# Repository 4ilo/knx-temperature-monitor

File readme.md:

# KNX temperature monitor

Custom Pt100 temperature probe interface to KNX.

This module will be used to monitor my pool temperature, and generate alarms if the pump, water treatement or the pool heating stops.

### Features
- STM32F0 microcontroller
- On module LCD temperature readout (Nokia 5110 Lcd)
- Tapko KIMaip KNX bus interface module
- MAX31865 RTD-to-Digital Converter
- Extra binary I/O

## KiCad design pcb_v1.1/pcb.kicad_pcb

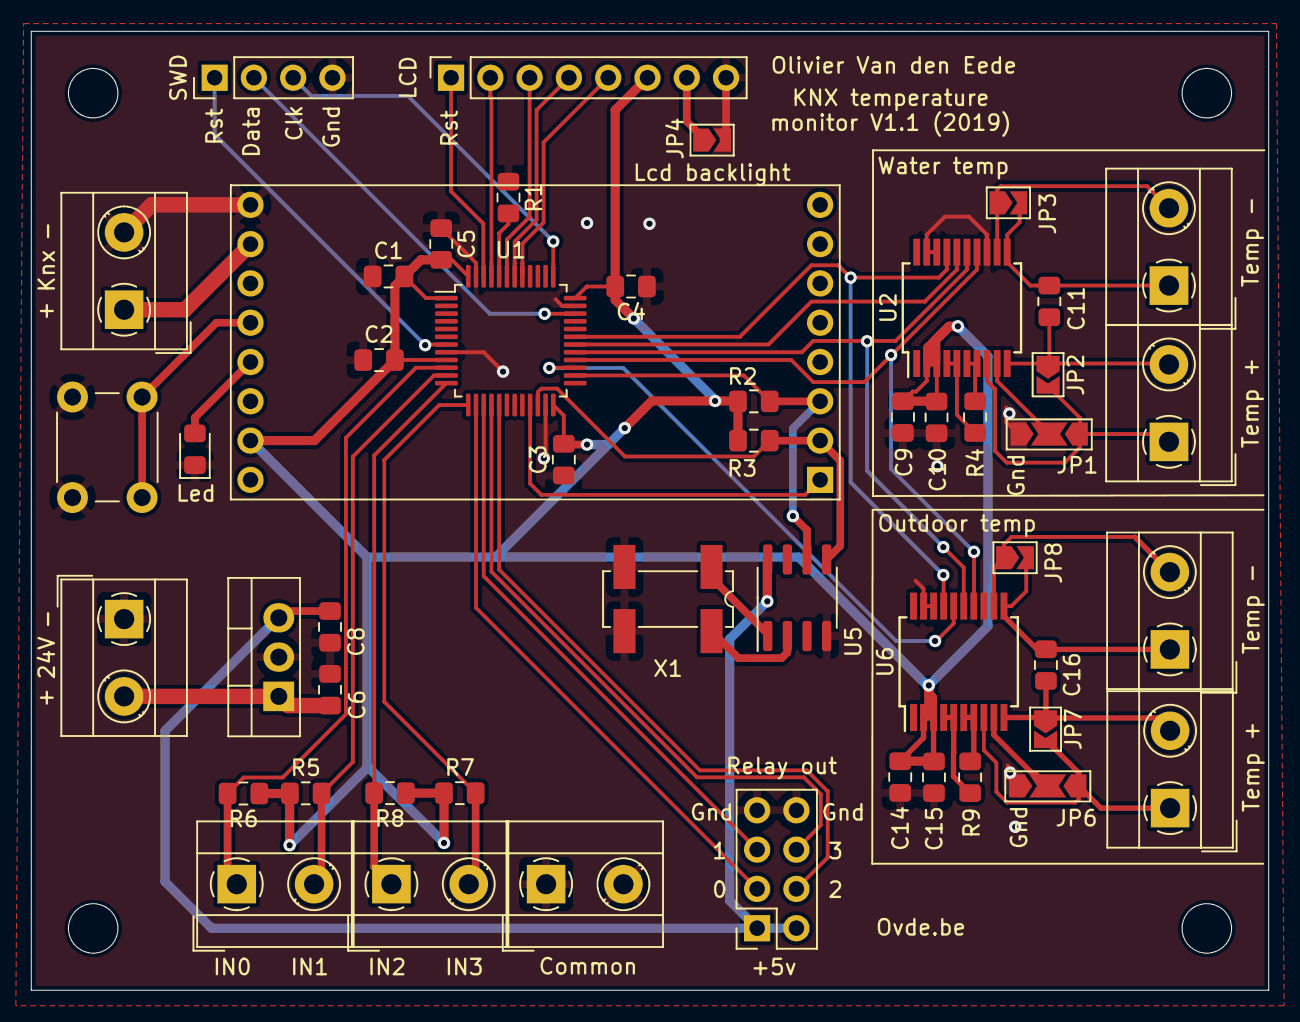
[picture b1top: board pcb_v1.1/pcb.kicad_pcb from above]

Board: 2 copper layers, 80.0 x 62.0 mm, 50 parts (0 on the bottom side), 49 nets.

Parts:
24V: 24v; TerminalBlock_MetzConnect_Type055_RT01502HDWU_1x02_P5.00mm_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
A1: KIMaip
C1, C2, C3, C4, C5, C8, C9, C10, C11, C14, C15, C16: 0.1uf; C_0805_2012Metric_Pad1.15x1.40mm_HandSolder
C6: 0.33uf; C_0805_2012Metric_Pad1.15x1.40mm_HandSolder
Common: Screw_Terminal_01x02; TerminalBlock_MetzConnect_Type055_RT01502HDWU_1x02_P5.00mm_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
J4, J5: Screw_Terminal_01x02; TerminalBlock_MetzConnect_Type055_RT01502HDWU_1x02_P5.00mm_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
JP1, JP6: SolderJumper_3_Open; SolderJumper-3_P2.0mm_Open_TrianglePad1.0x1.5mm_NumberLabels
JP2, JP3, JP4, JP7, JP8: SolderJumper_2_Open; SolderJumper-2_P1.3mm_Open_TrianglePad1.0x1.5mm
Knx: Knx; TerminalBlock_MetzConnect_Type055_RT01502HDWU_1x02_P5.00mm_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
LCD: Nokia 5110 LCD; PinSocket_1x08_P2.54mm_Vertical
Led: LED_ALT; LED_0805_2012Metric_Pad1.15x1.40mm_HandSolder
R1: 10k; R_0805_2012Metric_Pad1.15x1.40mm_HandSolder
R2, R3, R5, R6, R7, R8: 4k7; R_0805_2012Metric_Pad1.15x1.40mm_HandSolder
R4, R9: 420; R_0805_2012Metric_Pad1.15x1.40mm_HandSolder
Relay out: Relay out; PinSocket_2x04_P2.54mm_Vertical
SW1: SW_Push_Dual; SW_PUSH_6mm
SWD: SWD; PinHeader_1x04_P2.54mm_Vertical
Temp +: Screw_Terminal_01x02; TerminalBlock_MetzConnect_Type055_RT01502HDWU_1x02_P5.00mm_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
Temp +#2: Screw_Terminal_01x02; TerminalBlock_MetzConnect_Type055_RT01502HDWU_1x02_P5.00mm_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
Temp -: Screw_Terminal_01x02; TerminalBlock_MetzConnect_Type055_RT01502HDWU_1x02_P5.00mm_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
Temp -#2: Screw_Terminal_01x02; TerminalBlock_MetzConnect_Type055_RT01502HDWU_1x02_P5.00mm_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
U1: STM32F072C8Tx; LQFP-48_7x7mm_P0.5mm
U2, U6: MAX31865; SSOP-20_5.3x7.2mm_P0.65mm
U3: LM7805_TO220; TO-220-3_Vertical
U5: DS1307Z+; SOIC-8_3.9x4.9mm_P1.27mm
X1: 32.768kHz; Crystal_SMD_SeikoEpson_MC306-4Pin_8.0x3.2mm_HandSoldering

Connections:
+3V3: A1.15, C1.2, C2.2, C3.2, C4.2, C5.2, C9.2, C10.2, C14.2, C15.2, LCD.6, R2.1, R3.1, R5.1, R6.1, R7.1, R8.1, U1.1, U1.9, U1.24, U1.36, U1.48, U2.2, U2.3, U6.2, U6.3
+5V: C8.2, Relay out.1, Relay out.2, U3.3, U5.8
+24V: 24V.2, C6.2, U3.1
/BIN_0: J4.1, R6.2, U1.10
/BIN_1: J4.2, R5.2, U1.11
/BIN_2: J5.1, R8.2, U1.12
/BIN_3: J5.2, R7.2, U1.13
/CLK_1: U1.29, U2.15, U6.15
/DRDY: A1.1, U1.21
/Key: A1.12, SW1.1
/LCD_CE: LCD.2, U1.45
/LCD_CLK: LCD.5, U1.41
/LCD_DATA: LCD.4, U1.42
/LCD_DC: LCD.3, U1.43
/LCD_RST: LCD.1, U1.46
/MISO_1: U1.31, U2.17, U6.17
/MOSI_1: U1.28, U2.14, U6.14
/NRST: SWD.1, U1.7
/OUT_0: Relay out.3, U1.14
/OUT_1: Relay out.5, U1.15
/OUT_2: Relay out.4, U1.17
/OUT_3: Relay out.6, U1.16
/SCL: A1.3, R2.2, U1.26, U5.6
/SDA: A1.2, R3.2, U1.22, U5.5
/SS_1: U1.30, U2.16
/SS_2: U1.27, U6.16
/SWDCLK: SWD.3, U1.37
/SWDIO: SWD.2, U1.34
GND: 24V.1, A1.9, C1.1, C2.1, C3.1, C4.1, C5.1, C6.1, C8.1, C9.1, C10.1, C14.1, C15.1, Common.1, Common.2, JP1.3, JP4.2, JP6.3, Knx.2, LCD.8, Led.1, R1.1, Relay out.7, Relay out.8, SW1.2, SWD.4, U1.8, U1.23, U1.35, U1.47, U2.13, U2.18, U2.19, U3.2, U5.4, U6.13, U6.18, U6.19, X1.2, X1.3
unnamed: A1.10, Knx.1
unnamed: A1.13, Led.2
unnamed: C11.1, JP2.1, Temp +.2, U2.10
unnamed: C11.2, JP3.2, Temp -.1, U2.11
unnamed: C16.1, JP7.1, Temp +#2.2, U6.10
unnamed: C16.2, JP8.2, Temp -#2.1, U6.11
unnamed: JP4.1, LCD.7
unnamed: JP1.1, JP2.2, Temp +.1, U2.8
unnamed: JP3.1, Temp -.2, U2.12
unnamed: JP6.1, JP7.2, Temp +#2.1, U6.8
unnamed: JP8.1, Temp -#2.2, U6.12
unnamed: JP1.2, U2.9
unnamed: JP6.2, U6.9
unnamed: R1.2, U1.44
unnamed: R4.1, U2.4, U2.5
unnamed: R4.2, U2.6, U2.7
unnamed: R9.1, U6.4, U6.5
unnamed: R9.2, U6.6, U6.7
unnamed: U5.1, X1.1
unnamed: U5.2, X1.4

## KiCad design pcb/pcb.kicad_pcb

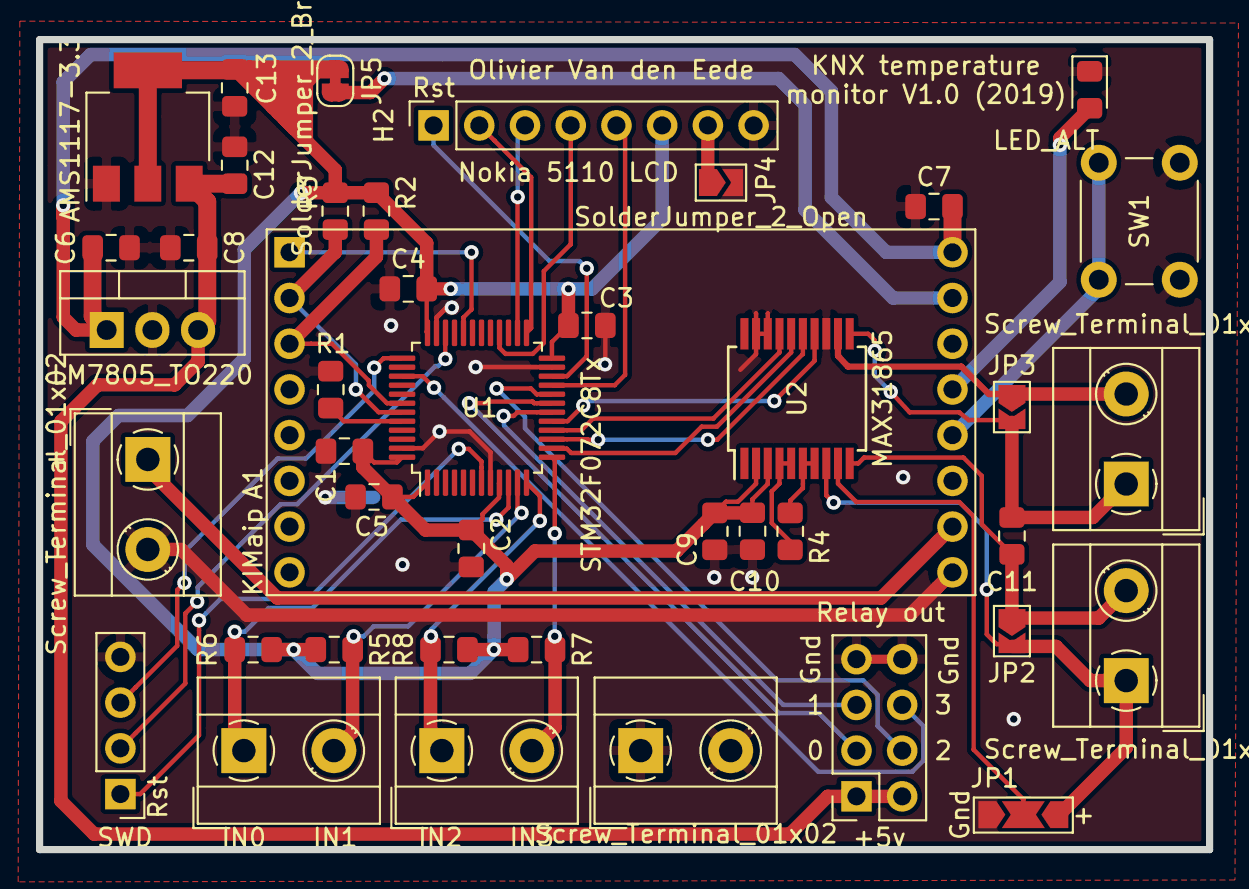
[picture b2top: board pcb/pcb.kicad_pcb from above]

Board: 2 copper layers, 65.0 x 45.0 mm, 42 parts (0 on the bottom side), 40 nets.

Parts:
A1: KIMaip
C1, C2, C3, C4, C5, C7, C8, C9, C10, C11: 0.1uf; C_0805_2012Metric_Pad1.15x1.40mm_HandSolder
C6: 0.33uf; C_0805_2012Metric_Pad1.15x1.40mm_HandSolder
C12, C13: 1uf; C_0805_2012Metric_Pad1.15x1.40mm_HandSolder
D1: LED_ALT; LED_0805_2012Metric_Pad1.15x1.40mm_HandSolder
H1: SWD; PinHeader_1x04_P2.54mm_Vertical
H2: Nokia 5110 LCD; PinSocket_1x08_P2.54mm_Vertical
H3: Relay out; PinSocket_2x04_P2.54mm_Vertical
J1, J2, J3, J4, J5, J6: Screw_Terminal_01x02; TerminalBlock_MetzConnect_Type055_RT01502HDWU_1x02_P5.00mm_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
JP1: SolderJumper_3_Open; SolderJumper-3_P2.0mm_Open_TrianglePad1.0x1.5mm_NumberLabels
JP2, JP3, JP4: SolderJumper_2_Open; SolderJumper-2_P1.3mm_Open_TrianglePad1.0x1.5mm
JP5: SolderJumper_2_Bridged; SolderJumper-2_P1.3mm_Bridged_RoundedPad1.0x1.5mm
R1: 10k; R_0805_2012Metric_Pad1.15x1.40mm_HandSolder
R2, R3, R5, R6, R7, R8: 4k7; R_0805_2012Metric_Pad1.15x1.40mm_HandSolder
R4: 420; R_0805_2012Metric_Pad1.15x1.40mm_HandSolder
SW1: SW_Push_Dual; SW_PUSH_6mm
U1: STM32F072C8Tx; LQFP-48_7x7mm_P0.5mm
U2: MAX31865; SSOP-20_5.3x7.2mm_P0.65mm
U3: LM7805_TO220; TO-220-3_Vertical
U4: AMS1117-3.3; SOT-223-3_TabPin2

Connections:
+3V3: C1.2, C2.2, C3.2, C4.2, C5.2, C9.2, C10.2, C13.2, H2.6, JP5.1, R2.1, R3.1, R5.1, R6.1, R7.1, R8.1, U1.1, U1.9, U1.24, U1.36, U1.48, U2.2, U2.3, U4.2
+5V: C8.2, C12.2, H3.1, H3.2, U3.3, U4.3
+12V: A1.16, C6.2, C7.2, U3.1
/BIN_0: J4.1, R6.2, U1.10
/BIN_1: J4.2, R5.2, U1.11
/BIN_2: J5.1, R8.2, U1.12
/BIN_3: J5.2, R7.2, U1.13
/CLK_1: U1.15, U2.15
/DRDY: A1.1, U1.32
/Key: A1.12, SW1.1
/LCD_CE: H2.2, U1.25
/LCD_CLK: H2.5, U1.21
/LCD_DATA: H2.4, U1.28
/LCD_DC: H2.3, U1.26
/LCD_RST: H2.1, U1.22
/MISO_1: U1.16, U2.17
/MOSI_1: U1.17, U2.14
/NRST: H1.1, U1.7
/OUT_0: H3.3, U1.19
/OUT_1: H3.5, U1.18
/OUT_2: H3.4, U1.20
/OUT_3: H3.6, U1.39
/SCL: A1.3, R2.2, U1.42
/SDA: A1.2, R3.2, U1.43
/SS_1: U1.14, U2.16
/SWDCLK: H1.3, U1.37
/SWDIO: H1.2, U1.34
GND: A1.9, C1.1, C2.1, C3.1, C4.1, C5.1, C6.1, C7.1, C8.1, C9.1, C10.1, C12.1, C13.1, D1.1, H1.4, H2.8, H3.7, H3.8, J3.2, J6.1, J6.2, JP1.3, JP4.2, R1.1, SW1.2, U1.8, U1.23, U1.35, U1.47, U2.13, U2.18, U2.19, U3.2, U4.1
unnamed: A1.10, J3.1
unnamed: A1.13, D1.2
unnamed: A1.15, JP5.2
unnamed: C11.1, J1.2, JP2.1, U2.10
unnamed: C11.2, J2.1, JP3.2, U2.11
unnamed: H2.7, JP4.1
unnamed: J1.1, JP1.1, JP2.2, U2.8
unnamed: J2.2, JP3.1, U2.12
unnamed: JP1.2, U2.9
unnamed: R1.2, U1.44
unnamed: R4.1, U2.4, U2.5
unnamed: R4.2, U2.6, U2.7

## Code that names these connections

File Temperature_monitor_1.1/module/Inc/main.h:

/* USER CODE BEGIN Header */
/**
  ******************************************************************************
  * @file           : main.h
  * @brief          : Header for main.c file.
  *                   This file contains the common defines of the application.
  ******************************************************************************
  * @attention
  *
  * <h2><center>&copy; Copyright (c) 2020 STMicroelectronics.
  * All rights reserved.</center></h2>
  *
  * This software component is licensed by ST under Ultimate Liberty license
  * SLA0044, the "License"; You may not use this file except in compliance with
  * the License. You may obtain a copy of the License at:
  *                             www.st.com/SLA0044
  *
  ******************************************************************************
  */
/* USER CODE END Header */

/* Define to prevent recursive inclusion -------------------------------------*/
#ifndef __MAIN_H
#define __MAIN_H

#ifdef __cplusplus
extern "C" {
#endif

/* Includes ------------------------------------------------------------------*/
#include "stm32f0xx_hal.h"

/* Private includes ----------------------------------------------------------*/
/* USER CODE BEGIN Includes */

/* USER CODE END Includes */

/* Exported types ------------------------------------------------------------*/
/* USER CODE BEGIN ET */

/* USER CODE END ET */

/* Exported constants --------------------------------------------------------*/
/* USER CODE BEGIN EC */

/* USER CODE END EC */

/* Exported macro ------------------------------------------------------------*/
/* USER CODE BEGIN EM */

/* USER CODE END EM */

/* Exported functions prototypes ---------------------------------------------*/
void Error_Handler(void);

/* USER CODE BEGIN EFP */

/* USER CODE END EFP */

/* Private defines -----------------------------------------------------------*/
#define BIN_0_Pin GPIO_PIN_0
#define BIN_0_GPIO_Port GPIOA
#define BIN_1_Pin GPIO_PIN_1
#define BIN_1_GPIO_Port GPIOA
#define BIN_2_Pin GPIO_PIN_2
#define BIN_2_GPIO_Port GPIOA
#define BIN_3_Pin GPIO_PIN_3
#define BIN_3_GPIO_Port GPIOA
#define OUT_0_Pin GPIO_PIN_4
#define OUT_0_GPIO_Port GPIOA
#define OUT_1_Pin GPIO_PIN_5
#define OUT_1_GPIO_Port GPIOA
#define OUT_3_Pin GPIO_PIN_6
#define OUT_3_GPIO_Port GPIOA
#define OUT_2_Pin GPIO_PIN_7
#define OUT_2_GPIO_Port GPIOA
#define DRDY_Pin GPIO_PIN_10
#define DRDY_GPIO_Port GPIOB
#define SS_2_Pin GPIO_PIN_14
#define SS_2_GPIO_Port GPIOB
#define MOSI_1_Pin GPIO_PIN_15
#define MOSI_1_GPIO_Port GPIOB
#define CLK_1_Pin GPIO_PIN_8
#define CLK_1_GPIO_Port GPIOA
#define SS_1_Pin GPIO_PIN_9
#define SS_1_GPIO_Port GPIOA
#define MISO_1_Pin GPIO_PIN_10
#define MISO_1_GPIO_Port GPIOA
#define LCD_CLK_Pin GPIO_PIN_5
#define LCD_CLK_GPIO_Port GPIOB
#define LCD_DATA_Pin GPIO_PIN_6
#define LCD_DATA_GPIO_Port GPIOB
#define LCD_DC_Pin GPIO_PIN_7
#define LCD_DC_GPIO_Port GPIOB
#define LCD_CE_Pin GPIO_PIN_8
#define LCD_CE_GPIO_Port GPIOB
#define LCD_RST_Pin GPIO_PIN_9
#define LCD_RST_GPIO_Port GPIOB
/* USER CODE BEGIN Private defines */

/* USER CODE END Private defines */

#ifdef __cplusplus
}
#endif

#endif /* __MAIN_H */

/************************ (C) COPYRIGHT STMicroelectronics *****END OF FILE****/

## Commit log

2019-05-20 start schematic
2019-05-20 fix lib component
2019-05-21 schematic + pin layout
2019-05-21 Add readme
2019-05-21 assign footprints
2019-05-21 custom footprint
2019-05-22 pcb layout
2019-05-22 pcb routed
2019-05-22 pcb klaar
2019-05-23 pcb ordered
2019-06-18 lcd working
2019-06-18 working max31865
2019-06-19 read binary inputs
2019-06-20 bus communication
2019-06-20 add rdry trace to pcb
2019-06-27 avg temperature fix
2019-06-29 update schematic
2019-07-01 pcb v1.1 component placement
2019-07-01 pcb done
2019-11-09 hello world on board
2020-02-23 add watchdog timer reset
2020-02-23 remove build
2020-05-24 dockerized v1.1 build with freertos
2020-05-24 create github action
2020-05-24 fix github action
2020-05-24 remove it from docker run
2020-05-24 docker root user in ci
2020-05-24 Add ci badge
2020-06-13 Basic io inputs
2020-06-14 Add first logic tests
2020-06-14 remove submodule
2020-06-14 Fix unity
2020-06-14 implement + test most logic
2020-06-14 finish logic + tests
2020-06-14 add missing field
2020-07-19 Read outside temp
2020-07-19 Compute temp with rolling average
2020-08-01 Read all inputs, run logic, send and read from knx and set outputs
2020-08-02 set max31865 in reset state before init
2020-08-02 increase wait times
2020-08-03 Activate pump_low when pump_high is 1
2020-08-03 disable pump_low when pump_high is low
2020-08-04 send pump low/high to knx
2020-08-04 Only send alarms when status changed
2020-08-08 Send pump error status over bus
2020-08-08 send always
2020-08-09 revert send always
2020-08-10 Don't reset alarm when pump is inactive
2020-08-10 add cppcheck
